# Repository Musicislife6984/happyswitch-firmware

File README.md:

# HappySwitch
Open Source MIDI Amp Controller

https://happyswitch.github.io/

## HappySwitch gives a MIDI input to your legacy guitar or bass amp

With HappySwitch you can control your midiless guitar or bass amp through any MIDI devices. Stop dancing on your pedals and bring your live performance to the next level with HappySwitch!

HappySwitch receives the MIDI Program Change messages and applies the stored config to your amp.

This prototype was expecially developed to work with MESA/Boogie® Dual & Triple Rectifier™ which have a proprietary footswitch interface (7 DIN) but, you can hack it to control every amp with a standard footswitch 1/4" jack interfaces.

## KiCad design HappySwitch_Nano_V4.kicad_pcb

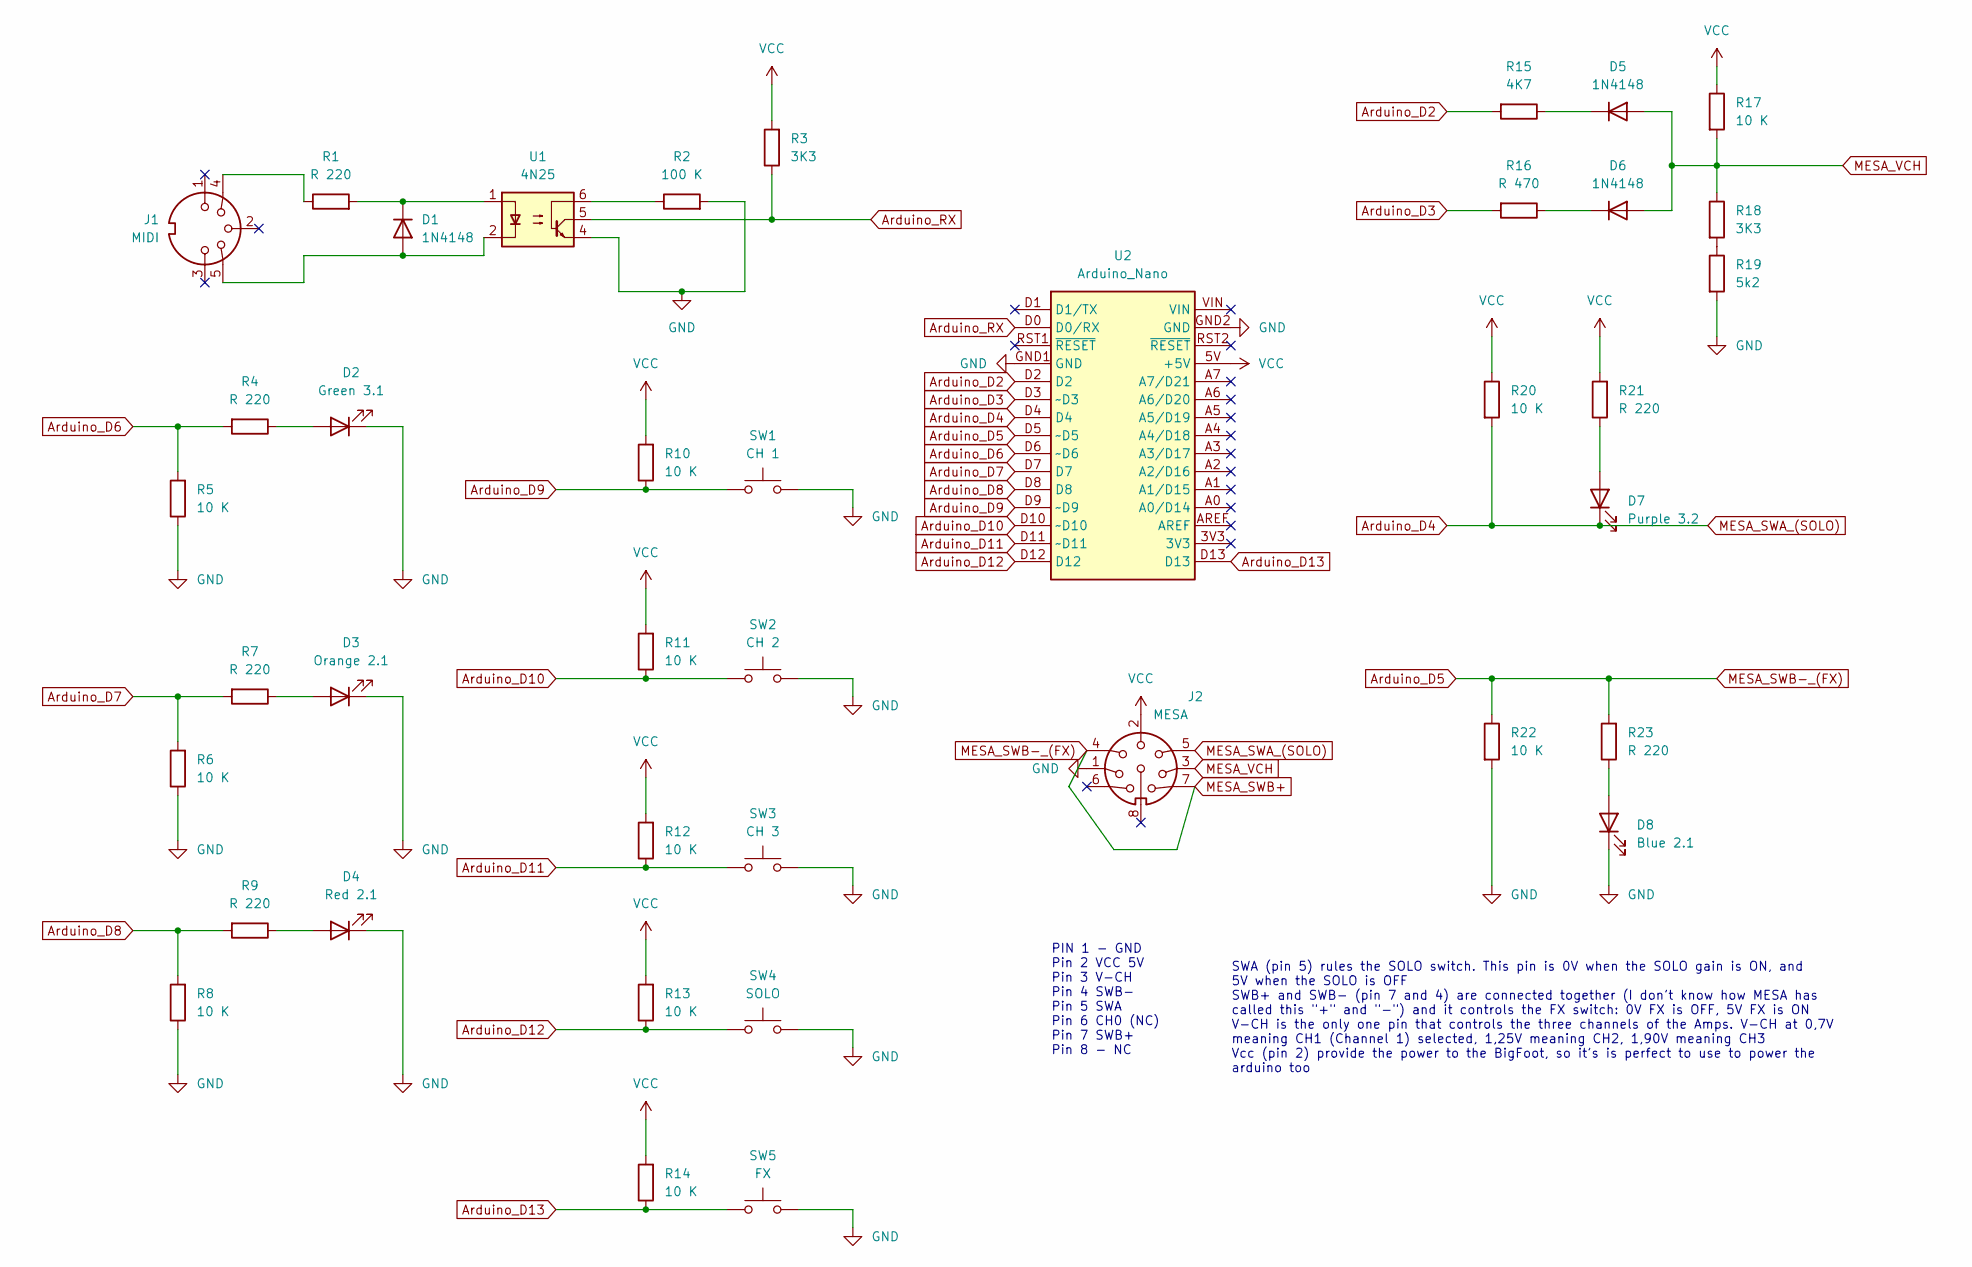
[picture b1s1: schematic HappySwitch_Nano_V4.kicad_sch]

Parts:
D1, D5, D6: 1N4148; D_DO-35_SOD27_P7.62mm_Horizontal
D2: Green 3.1; LED_D3.0mm
D3: Orange 2.1; LED_D3.0mm
D4: Red 2.1; LED_D3.0mm
D7: Purple 3.2; LED_D3.0mm
D8: Blue 2.1; LED_D3.0mm
J1: MIDI; PinHeader_1x05_P2.54mm_Vertical
J2: MESA; PinHeader_1x08_P2.54mm_Vertical
R1, R4, R7, R9, R21, R23: R 220; R_Axial_DIN0207_L6.3mm_D2.5mm_P7.62mm_Horizontal
R2: 100 K; R_Axial_DIN0207_L6.3mm_D2.5mm_P7.62mm_Horizontal
R3, R18: 3K3; R_Axial_DIN0207_L6.3mm_D2.5mm_P7.62mm_Horizontal
R5, R6, R8, R10, R11, R12, R13, R14, R17, R20, R22: 10 K; R_Axial_DIN0207_L6.3mm_D2.5mm_P7.62mm_Horizontal
R15: 4K7; R_Axial_DIN0207_L6.3mm_D2.5mm_P7.62mm_Horizontal
R16: R 470; R_Axial_DIN0207_L6.3mm_D2.5mm_P7.62mm_Horizontal
R19: 5k2; R_Axial_DIN0207_L6.3mm_D2.5mm_P7.62mm_Horizontal
SW1: CH 1; PinHeader_1x02_P2.54mm_Vertical
SW2: CH 2; PinHeader_1x02_P2.54mm_Vertical
SW3: CH 3; PinHeader_1x02_P2.54mm_Vertical
SW4: SOLO; PinHeader_1x02_P2.54mm_Vertical
SW5: FX; PinHeader_1x02_P2.54mm_Vertical
U1: 4N25; DIP-6_W7.62mm
U2: Arduino_Nano; Arduino_Nano_Socket

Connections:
Arduino_D2: R15.2, U2.D2
Arduino_D3: R16.2, U2.D3 (~D3)
Arduino_D4: D7.1 (K), J2.5, R20.2, U2.D4
Arduino_D5: J2.4, J2.7, R22.1, R23.2, U2.D5 (~D5)
Arduino_D6: R4.2, R5.2, U2.D6 (~D6)
Arduino_D7: R6.2, R7.2, U2.D7
Arduino_D8: R8.2, R9.2, U2.D8
Arduino_D9: R10.1, SW1.1, U2.D9 (~D9)
Arduino_D10: R11.1, SW2.1, U2.D10 (~D10)
Arduino_D11: R12.1, SW3.1, U2.D11 (~D11)
Arduino_D12: R13.1, SW4.1, U2.D12
Arduino_D13: R14.1, SW5.1, U2.D13
Arduino_RX: R3.1, U1.5, U2.D0 (D0/RX)
GND: D2.1 (K), D3.1 (K), D4.1 (K), D8.1 (K), J2.1, R2.2, R5.1, R6.1, R8.1, R19.2, R22.2, SW1.2, SW2.2, SW3.2, SW4.2, SW5.2, U1.4, U2.GND1 (GND), U2.GND2 (GND)
MESA_VCH: D5.2 (A), D6.2 (A), J2.3, R17.2, R18.1
unnamed: D1.2 (A), J1.5, U1.2
unnamed: D1.1 (K), R1.2, U1.1
unnamed: D2.2 (A), R4.1
unnamed: D3.2 (A), R7.1
unnamed: D4.2 (A), R9.1
unnamed: D5.1 (K), R15.1
unnamed: D6.1 (K), R16.1
unnamed: D7.2 (A), R21.1
unnamed: D8.2 (A), R23.1
unnamed: J1.4, R1.1
unnamed: R2.1, U1.6
unnamed: R18.2, R19.1
VCC: J2.2, R3.2, R10.2, R11.2, R12.2, R13.2, R14.2, R17.1, R20.1, R21.2, U2.5V (+5V)

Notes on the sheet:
PIN 1 - GND Pin 2 VCC 5V Pin 3 V-CH Pin 4 SWB- Pin 5 SWA Pin 6 CH0 (NC) Pin 7 SWB+ Pin 8 - NC
SWA (pin 5) rules the SOLO switch. This pin is 0V when the SOLO gain is ON, and 5V when the SOLO is OFF SWB+ and SWB- (pin 7 and 4) are connected together (I don't know how MESA has called this "+" and "-") and it controls the FX switch: 0V FX is OFF, 5V FX is ON V-CH is the only one pin that contr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

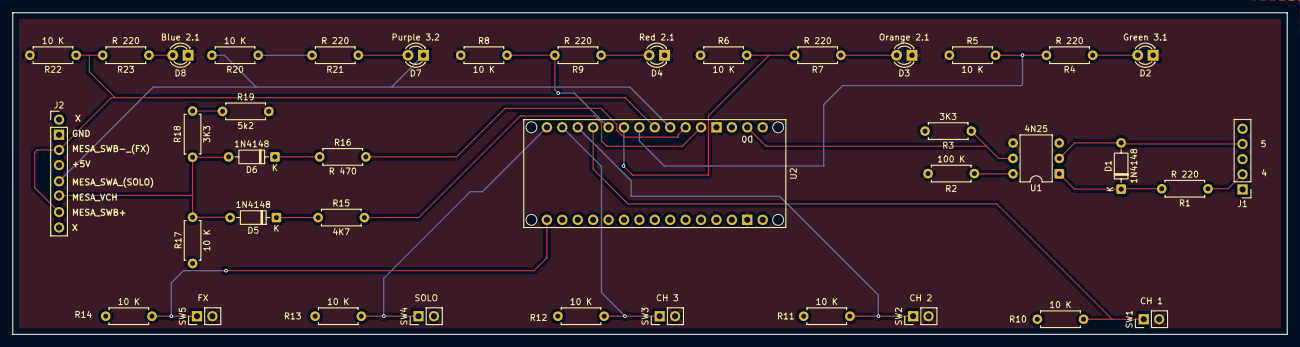
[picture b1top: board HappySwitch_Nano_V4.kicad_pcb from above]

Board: 2 copper layers, 210.0 x 53.0 mm, 40 parts (0 on the bottom side), 28 nets.

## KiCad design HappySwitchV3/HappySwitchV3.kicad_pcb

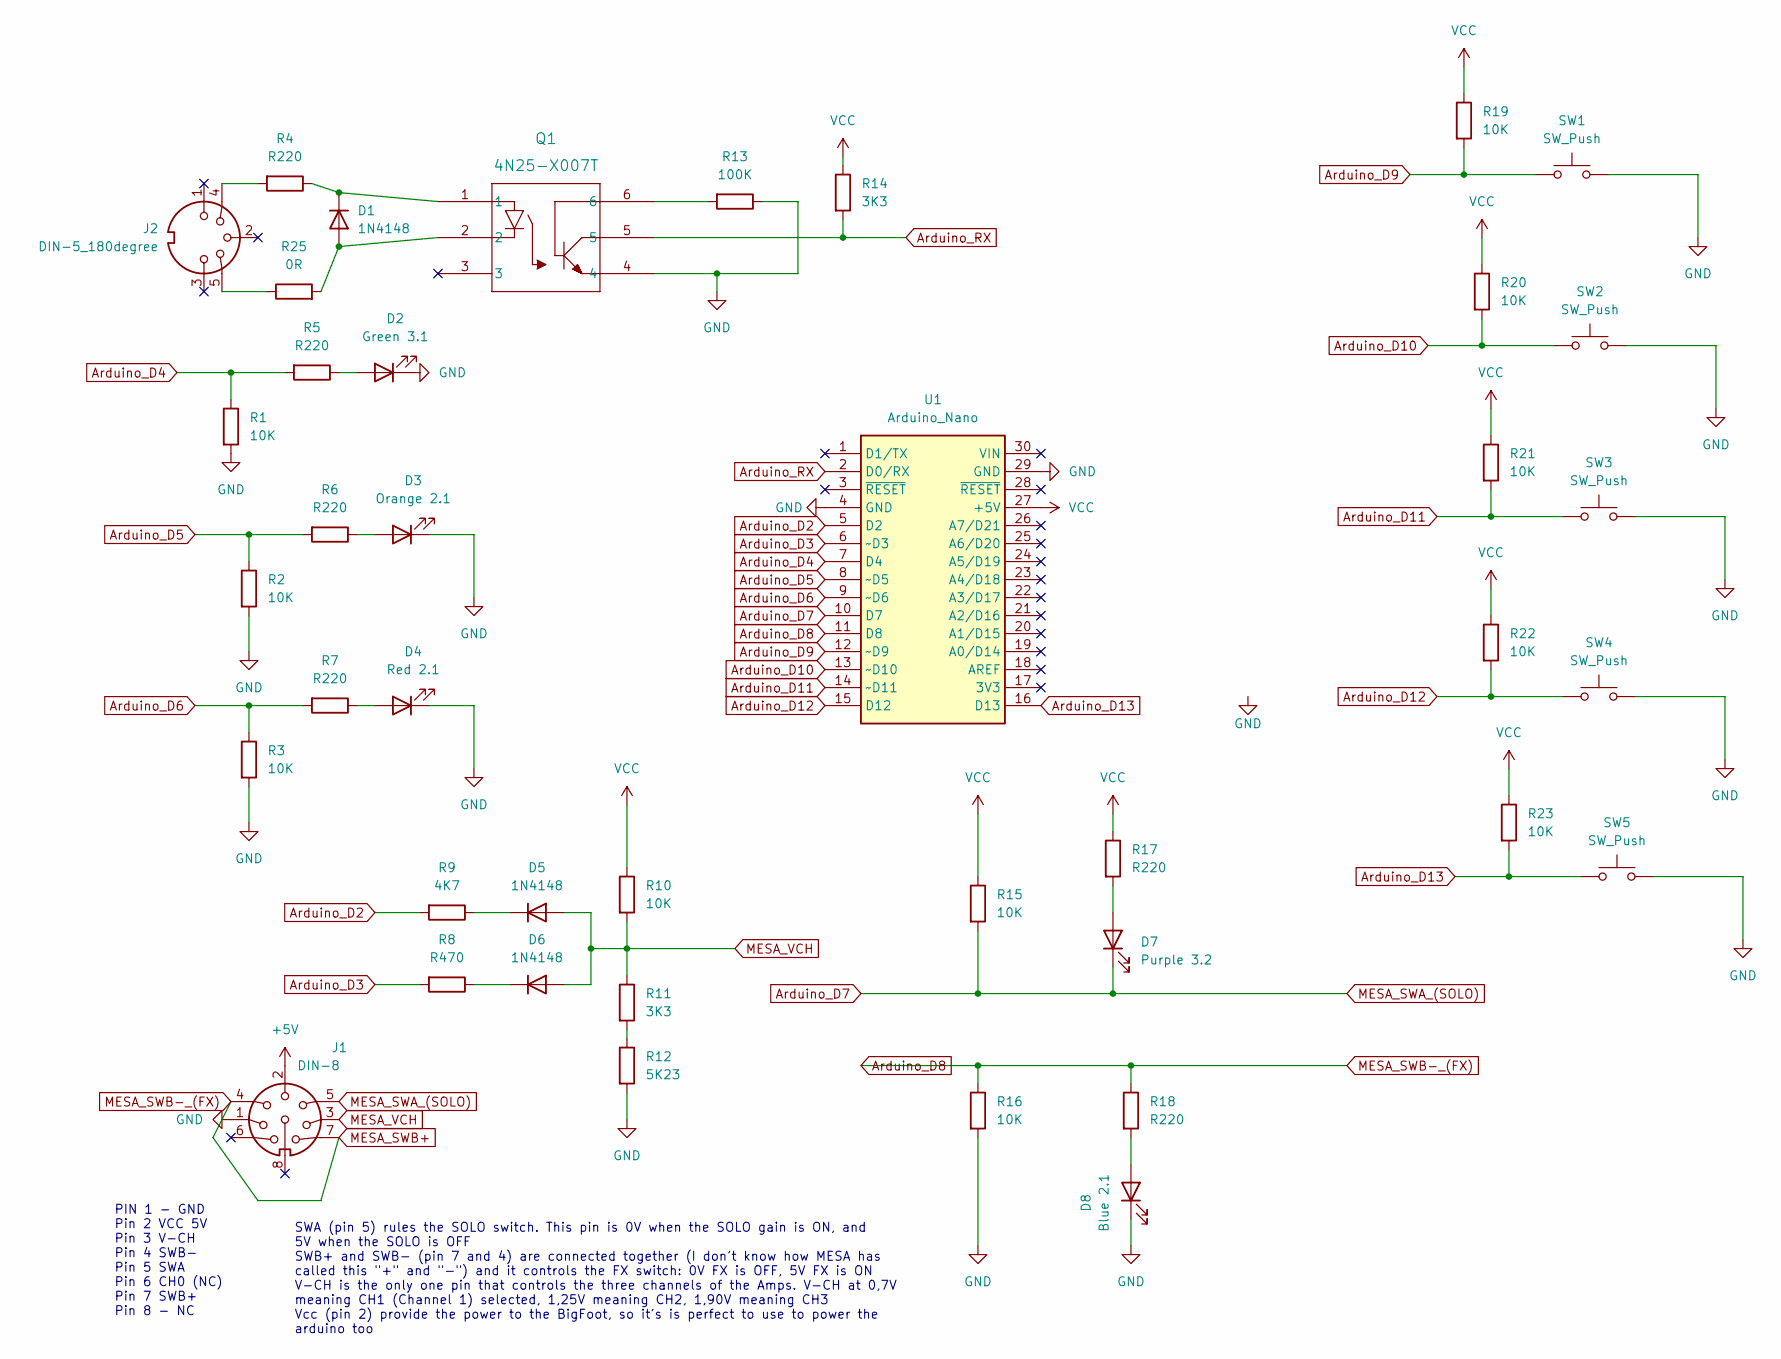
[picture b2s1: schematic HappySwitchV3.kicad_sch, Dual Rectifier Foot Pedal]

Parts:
D1, D5, D6: 1N4148; SOD123_DIO; MPN 1N4148W; DigiKey Part Number 4878-1N4148WCT-ND
D2: Green 3.1; LED_D5.0mm
D3: Orange 2.1; LED_D5.0mm
D4: Red 2.1; LED_D5.0mm
D7: Purple 3.2; LED_D5.0mm
D8: Blue 2.1; LED_D5.0mm
J1: DIN-8; PinHeader_1x08_P2.54mm_Vertical
J2: DIN-5_180degree; PinHeader_1x05_P2.54mm_Vertical
Q1: 4N25-X007T; X007_VIS; MPN 4N25-X007T; DigiKey Part Number 4N25-X007TCT-ND
R1, R2, R3, R10, R15, R16, R19, R20, R21, R22, R23: 10K; R_0805_2012Metric; MPN ERA-6VEB1002V; DigiKey Part Number 10-ERA-6VEB1002VCT-ND
R4, R5, R6, R7, R17, R18: R220; R_0805_2012Metric; MPN ERJ-PB6B2200V; DigiKey Part Number P20516CT-ND
R8: R470; R_0805_2012Metric; MPN ERA-6VEB4700V; DigiKey Part Number 10-ERA-6VEB4700VCT-ND
R9: 4K7; R_0805_2012Metric; MPN ERA-6VEB4701V; DigiKey Part Number 10-ERA-6VEB4701VCT-ND
R11, R14: 3K3; R_0805_2012Metric; MPN ERJ-PB6D3301V; DigiKey Part Number P21076CT-ND
R12: 5K23; R_0805_2012Metric; MPN ERJ-PB6B5231V; DigiKey Part Number P20676CT-ND
R13: 100K; R_0805_2012Metric; MPN ERA-6VEB1003V; DigiKey Part Number 10-ERA-6VEB1003VCT-ND
R25: 0R; R_0805_2012Metric; MPN ERJ-6GEY0R00V; DigiKey Part Number P0.0ACT-ND
SW1, SW2, SW3, SW4, SW5: SW_Push; PinHeader_1x02_P2.54mm_Vertical
U1: Arduino_Nano

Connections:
+5V: J1.2
Arduino_D2: R9.2, U1.5 (D2)
Arduino_D3: R8.2, U1.6 (~D3)
Arduino_D4: R1.1, R5.2, U1.7 (D4)
Arduino_D5: R2.1, R6.2, U1.8 (~D5)
Arduino_D6: R3.1, R7.2, U1.9 (~D6)
Arduino_D7: D7.1 (K), J1.5, R15.2, U1.10 (D7)
Arduino_D8: J1.4, J1.7, R16.1, R18.1, U1.11 (D8)
Arduino_D9: R19.2, SW1.1, U1.12 (~D9)
Arduino_D10: R20.2, SW2.1, U1.13 (~D10)
Arduino_D11: R21.2, SW3.1, U1.14 (~D11)
Arduino_D12: R22.2, SW4.1, U1.15 (D12)
Arduino_D13: R23.2, SW5.1, U1.16 (D13)
Arduino_RX: Q1.5, R14.2, U1.2 (D0/RX)
GND: D2.1 (K), D3.1 (K), D4.1 (K), D8.1 (K), J1.1, Q1.4, R1.2, R2.2, R3.2, R12.2, R13.1, R16.2, SW1.2, SW2.2, SW3.2, SW4.2, SW5.2, U1.4 (GND), U1.29 (GND)
MESA_VCH: D5.2 (A), D6.2 (A), J1.3, R10.2, R11.1
unnamed: D1.1 (K), Q1.1, R4.1
unnamed: D1.2 (A), Q1.2, R25.2
unnamed: D2.2 (A), R5.1
unnamed: D3.2 (A), R6.1
unnamed: D4.2 (A), R7.1
unnamed: D5.1 (K), R9.1
unnamed: D6.1 (K), R8.1
unnamed: D7.2 (A), R17.2
unnamed: D8.2 (A), R18.2
unnamed: J2.4, R4.2
unnamed: J2.5, R25.1
unnamed: Q1.6, R13.2
unnamed: R11.2, R12.1
VCC: R10.1, R14.1, R15.1, R17.1, R19.1, R20.1, R21.1, R22.1, R23.1, U1.27 (+5V)

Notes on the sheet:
SWA (pin 5) rules the SOLO switch. This pin is 0V when the SOLO gain is ON, and 5V when the SOLO is OFF SWB+ and SWB- (pin 7 and 4) are connected together (I don't know how MESA has called this "+" and "-") and it controls the FX switch: 0V FX is OFF, 5V FX is ON V-CH is the only one pin that contr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
PIN 1 - GND Pin 2 VCC 5V Pin 3 V-CH Pin 4 SWB- Pin 5 SWA Pin 6 CH0 (NC) Pin 7 SWB+ Pin 8 - NC

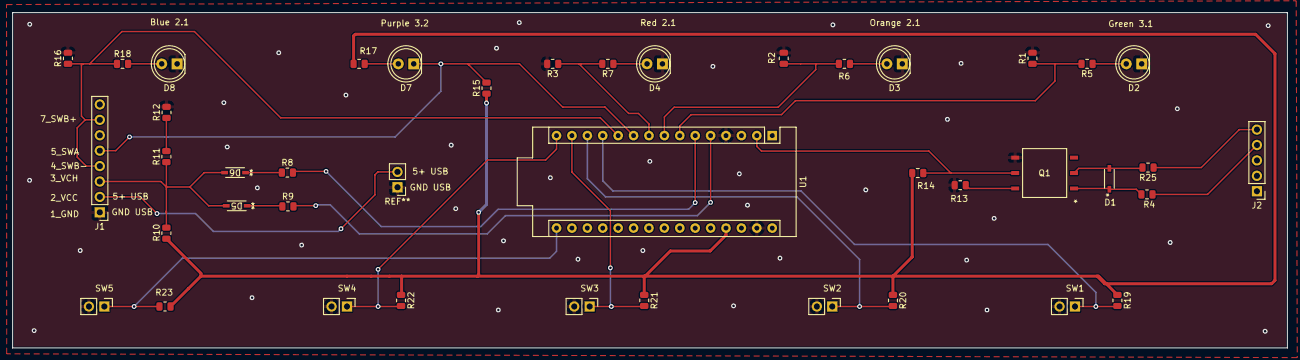
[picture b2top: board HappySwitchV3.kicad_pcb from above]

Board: 2 copper layers, 210.1 x 55.3 mm, 41 parts (0 on the bottom side), 29 nets.

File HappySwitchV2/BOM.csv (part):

"Source:","/Users/seanmartz/Documents/HappySwitchV2/HappySwitchV2.kicad_sch"
"Date:","Sunday, September 01, 2024 at 06:22:37 PM"
"Tool:","Eeschema (6.0.0-0)"
"Generator:","/Applications/KiCad/KiCad.app/Contents/SharedSupport/plugins/bom_csv_grouped_by_value.py"
"Component Count:","41"

"Individual Components:"

"Item","Qty","Reference(s)","Value","LibPart","Footprint","Datasheet","DigiKey Part Number ","MPN","Manufacturer"
"","","D1","1N4148","Diode:1N4148","1N4148W-13-L:SOD123_DIO","https://assets.nexperia.com/documents/data-sheet/1N4148_1N4448.pdf","4878-1N4148WCT-ND","1N4148W","Diotec Semiconductor"
"","","D2","Green 3.1","Device:LED","LED_THT:LED_D5.0mm","~","","",""
"","","D3","Orange 2.1","Device:LED","LED_THT:LED_D5.0mm","~","","",""
"","","D4","Red 2.1","Device:LED","LED_THT:LED_D5.0mm","~","","",""
"","","D5","1N4148","Diode:1N4148","1N4148W-13-L:SOD123_DIO","https://assets.nexperia.com/documents/data-sheet/1N4148_1N4448.pdf","4878-1N4148WCT-ND","1N4148W","Diotec Semiconductor"
"","","D6","1N4148","Diode:1N4148","1N4148W-13-L:SOD123_DIO","https://assets.nexperia.com/documents/data-sheet/1N4148_1N4448.pdf","4878-1N4148WCT-ND","1N4148W","Diotec Semiconductor"
"","","D7","Purple 3.2","Device:LED","LED_THT:LED_D5.0mm","~","","",""
"","","D8","Blue 2.1","Device:LED","LED_THT:LED_D5.0mm","~","","",""
"","","J1","DIN-8","Connector:DIN-8","Connector_PinHeader_2.54mm:PinHeader_1x08_P2.54mm_Vertical","http://www.mouser.com/ds/2/18/40_c091_abd_e-75918.pdf","","",""
"","","J2","DIN-5_180degree","Connector:DIN-5_180degree","Connector_PinHeader_2.54mm:PinHeader_1x05_P2.54mm_Vertical","http://www.mouser.com/ds/2/18/40_c091_abd_e-75918.pdf","","",""
"","","Q1","4N25-X007T","4n25-x007t:4N25-X007T","4n25-x007t:X007_VIS","4N25-X007T","4N25-X007TCT-ND","4N25-X007T","Vishay Semiconductor Opto Division"
"","","R1","10K","Device:R","Resistor_SMD:R_0805_2012Metric","~","10-ERA-6VEB1002VCT-ND","ERA-6VEB1002V","Panasonic Electronic Components"
"","","R2","10K","Device:R","Resistor_SMD:R_0805_2012Metric","(sheet_instances","10-ERA-6VEB1002VCT-ND","ERA-6VEB1002V","Panasonic Electronic Components"
"","","R3","10K","Device:R","Resistor_SMD:R_0805_2012Metric","~","10-ERA-6VEB1002VCT-ND","ERA-6VEB1002V","Panasonic Electronic Components"
"","","R4","R220","Device:R","Resistor_SMD:R_0805_2012Metric","~","P20516CT-ND","ERJ-PB6B2200V","Panasonic Electronic Components"
"","","R5","R220","Device:R","Resistor_SMD:R_0805_2012Metric","~","P20516CT-ND","ERJ-PB6B2200V","Panasonic Electronic Components"
"","","R6","R220","Device:R","Resistor_SMD:R_0805_2012Metric","~","P20516CT-ND","ERJ-PB6B2200V","Panasonic Electronic Components"
"","","R7","R220","Device:R","Resistor_SMD:R_0805_2012Metric","~","P20516CT-ND","ERJ-PB6B2200V","Panasonic Electronic Components"
"","","R8","R470","Device:R","Resistor_SMD:R_0805_2012Metric","~","10-ERA-6VEB4700VCT-ND","ERA-6VEB4700V","Panasonic Electronic Components"
"","","R9","4K7","Device:R","Resistor_SMD:R_0805_2012Metric","~","10-ERA-6VEB4701VCT-ND","ERA-6VEB4701V","Panasonic Electronic Components"
"","","R10","10K","Device:R","Resistor_SMD:R_0805_2012Metric","~","10-ERA-6VEB1002VCT-ND","ERA-6VEB1002V","Panasonic Electronic Components"
"","","R11","3K3","Device:R","Resistor_SMD:R_0805_2012Metric","~","P21076CT-ND","ERJ-PB6D3301V","Panasonic Electronic Components"
"","","R12","5K23","Device:R","Resistor_SMD:R_0805_2012Metric","~","P20676CT-ND","ERJ-PB6B5231V","Panasonic Electronic Components"
"","","R13","100K","Device:R","Resistor_SMD:R_0805_2012Metric","~","10-ERA-6VEB1003VCT-ND","ERA-6VEB1003V","Panasonic Electronic Components"
"","","R14","3K3","Device:R","Resistor_SMD:R_0805_2012Metric","~","P21076CT-ND","ERJ-PB6D3301V","Panasonic Electronic Components"
"","","R15","10K","Device:R","Resistor_SMD:R_0805_2012Metric","~","10-ERA-6VEB1002VCT-ND","ERA-6VEB1002V","Panasonic Electronic Components"
"","","R16","10K","Device:R","Resistor_SMD:R_0805_2012Metric","~","10-ERA-6VEB1002VCT-ND","ERA-6VEB1002V","Panasonic Electronic Components"
"","","R17","R220","Device:R","Resistor_SMD:R_0805_2012Metric","~","P20516CT-ND","ERJ-PB6B2200V","Panasonic Electronic Components"
"","","R18","R220","Device:R","Resistor_SMD:R_0805_2012Metric","~","P20516CT-ND","ERJ-PB6B2200V","Panasonic Electronic Components"
"","","R19","10K","Device:R","Resistor_SMD:R_0805_2012Metric","~","10-ERA-6VEB1002VCT-ND","ERA-6VEB1002V","Panasonic Electronic Components"
"","","R20","10K","Device:R","Resistor_SMD:R_0805_2012Metric","~","10-ERA-6VEB1002VCT-ND","ERA-6VEB1002V","Panasonic Electronic Components"
"","","R21","10K","Device:R","Resistor_SMD:R_0805_2012Metric","~","10-ERA-6VEB1002VCT-ND","ERA-6VEB1002V","Panasonic Electronic Components"
"","","R22","10K","Device:R","Resistor_SMD:R_0805_2012Metric","~","10-ERA-6VEB1002VCT-ND","ERA-6VEB1002V","Panasonic Electronic Components"
"","","R23","10K","Device:R","Resistor_SMD:R_0805_2012Metric","~","10-ERA-6VEB1002VCT-ND","ERA-6VEB1002V","Panasonic Electronic Components"
"","","R25","0R","Device:R","Resistor_SMD:R_0805_2012Metric","~","P0.0ACT-ND","ERJ-6GEY0R00V","Panasonic Electronic Components"
"","","SW1","SW_Push","Switch:SW_Push","Connector_PinHeader_2.54mm:PinHeader_1x02_P2.54mm_Vertical","~","","",""
"","","SW2","SW_Push","Switch:SW_Push","Connector_PinHeader_2.54mm:PinHeader_1x02_P2.54mm_Vertical","~","","",""
"","","SW3","SW_Push","Switch:SW_Push","Connector_PinHeader_2.54mm:PinHeader_1x02_P2.54mm_Vertical","~","","",""
"","","SW4","SW_Push","Switch:SW_Push","Connector_PinHeader_2.54mm:PinHeader_1x02_P2.54mm_Vertical","~","","",""
"","","SW5","SW_Push","Switch:SW_Push","Connector_PinHeader_2.54mm:PinHeader_1x02_P2.54mm_Vertical","~","","",""
"","","U1","Sparkfun_Pro_Micro","Arduino:Sparkfun_Pro_Micro","Arduino:Sparkfun_Pro_Micro","https://www.sparkfun.com/products/12640","","",""



"Collated Components:"

"Item","Qty","Reference(s)","Value","LibPart","Footprint","Datasheet","DigiKey Part Number ","MPN","Manufacturer"
"1","3","D1, D5, D6","1N4148","Diode:1N4148","1N4148W-13-L:SOD123_DIO","https://assets.nexperia.com/documents/data-sheet/1N4148_1N4448.pdf","4878-1N4148WCT-ND","1N4148W","Diotec Semiconductor"
"2","1","D2","Green 3.1","Device:LED","LED_THT:LED_D5.0mm","~","","",""
"3","1","D3","Orange 2.1","Device:LED","LED_THT:LED_D5.0mm","~","","",""
"4","1","D4","Red 2.1","Device:LED","LED_THT:LED_D5.0mm","~","","",""
"5","1","D7","Purple 3.2","Device:LED","LED_THT:LED_D5.0mm","~","","",""
"6","1","D8","Blue 2.1","Device:LED","LED_THT:LED_D5.0mm","~","","",""
"7","1","J1","DIN-8","Connector:DIN-8","Connector_PinHeader_2.54mm:PinHeader_1x08_P2.54mm_Vertical","http://www.mouser.com/ds/2/18/40_c091_abd_e-75918.pdf","","",""
"8","1","J2","DIN-5_180degree","Connector:DIN-5_180degree","Connector_PinHeader_2.54mm:PinHeader_1x05_P2.54mm_Vertical","http://www.mouser.com/ds/2/18/40_c091_abd_e-75918.pdf","","",""
"9","1","Q1","4N25-X007T","4n25-x007t:4N25-X007T","4n25-x007t:X007_VIS","4N25-X007T","4N25-X007TCT-ND","4N25-X007T","Vishay Semiconductor Opto Division"
"10","11","R1, R2, R3, R10, R15, R16, R19, R20, R21, R22, R23","10K","Device:R","Resistor_SMD:R_0805_2012Metric","~","10-ERA-6VEB1002VCT-ND","ERA-6VEB1002V","Panasonic Electronic Components"
"11","6","R4, R5, R6, R7, R17, R18","R220","Device:R","Resistor_SMD:R_0805_2012Metric","~","P20516CT-ND","ERJ-PB6B2200V","Panasonic Electronic Components"
"12","1","R8","R470","Device:R","Resistor_SMD:R_0805_2012Metric","~","10-ERA-6VEB4700VCT-ND","ERA-6VEB4700V","Panasonic Electronic Components"
"13","1","R9","4K7","Device:R","Resistor_SMD:R_0805_2012Metric","~","10-ERA-6VEB4701VCT-ND","ERA-6VEB4701V","Panasonic Electronic Components"
"14","2","R11, R14","3K3","Device:R","Resistor_SMD:R_0805_2012Metric","~","P21076CT-ND","ERJ-PB6D3301V","Panasonic Electronic Components"
"15","1","R12","5K23","Device:R","Resistor_SMD:R_0805_2012Metric","~","P20676CT-ND","ERJ-PB6B5231V","Panasonic Electronic Components"
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
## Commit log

2024-09-02 Rename HappySwitchV2.csv to BOM.csv
2024-09-02 Add files via upload
    Uploaded completed Kicad
2026-01-09 blank slate
